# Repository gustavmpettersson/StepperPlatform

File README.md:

# StepperPlatform

This project considers a platform for moving microscopy samples. It is made as a Bachelor's thesis project at KTH. Usage instructions, drawings, and parts can be found in appendices.pdf

Contact me at gupet[a]kth.se or gustavpettersson[a]live.com

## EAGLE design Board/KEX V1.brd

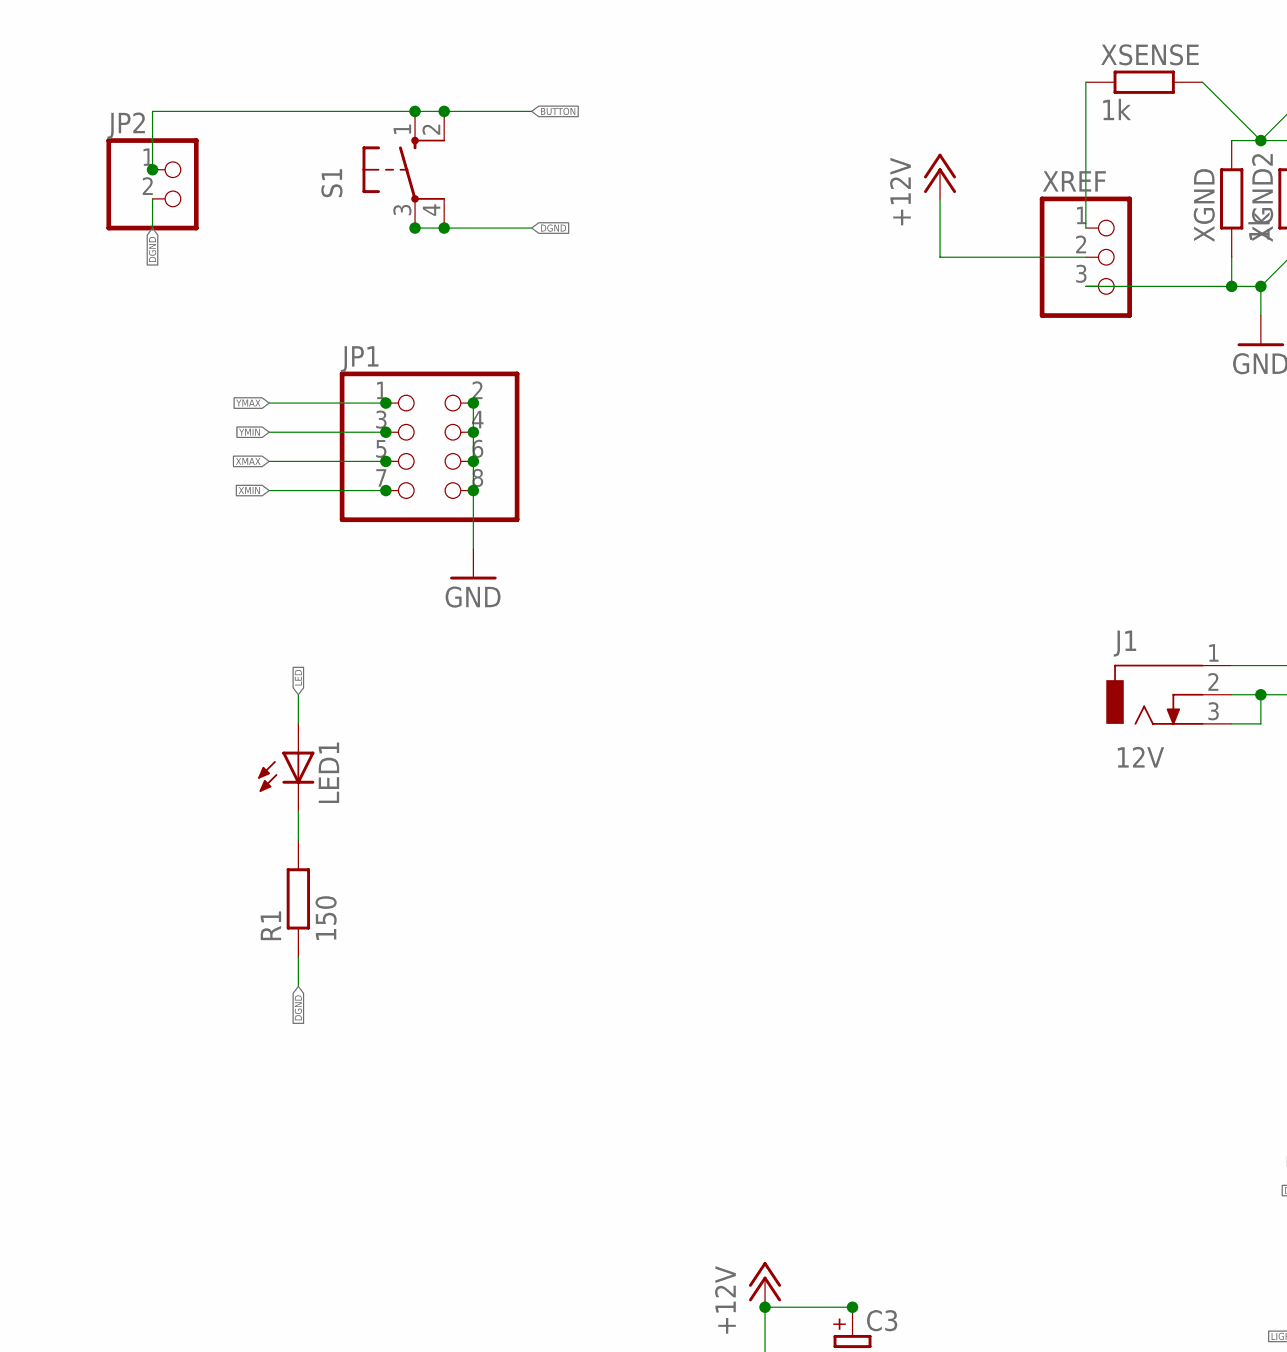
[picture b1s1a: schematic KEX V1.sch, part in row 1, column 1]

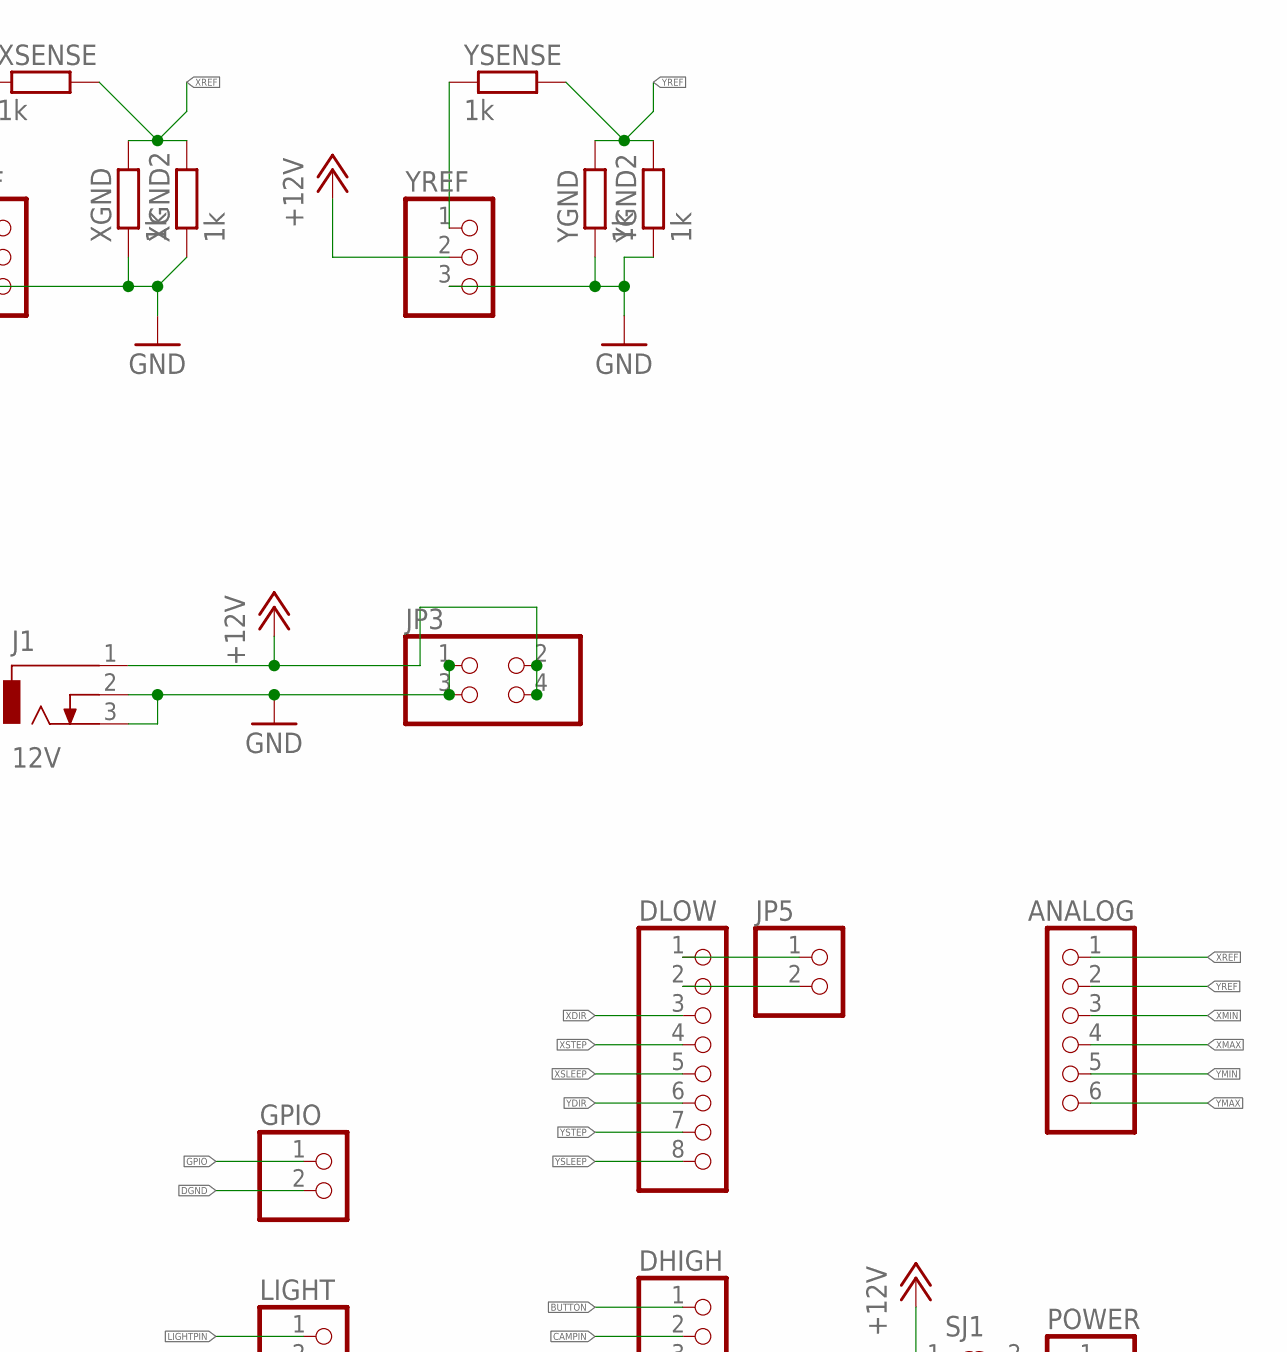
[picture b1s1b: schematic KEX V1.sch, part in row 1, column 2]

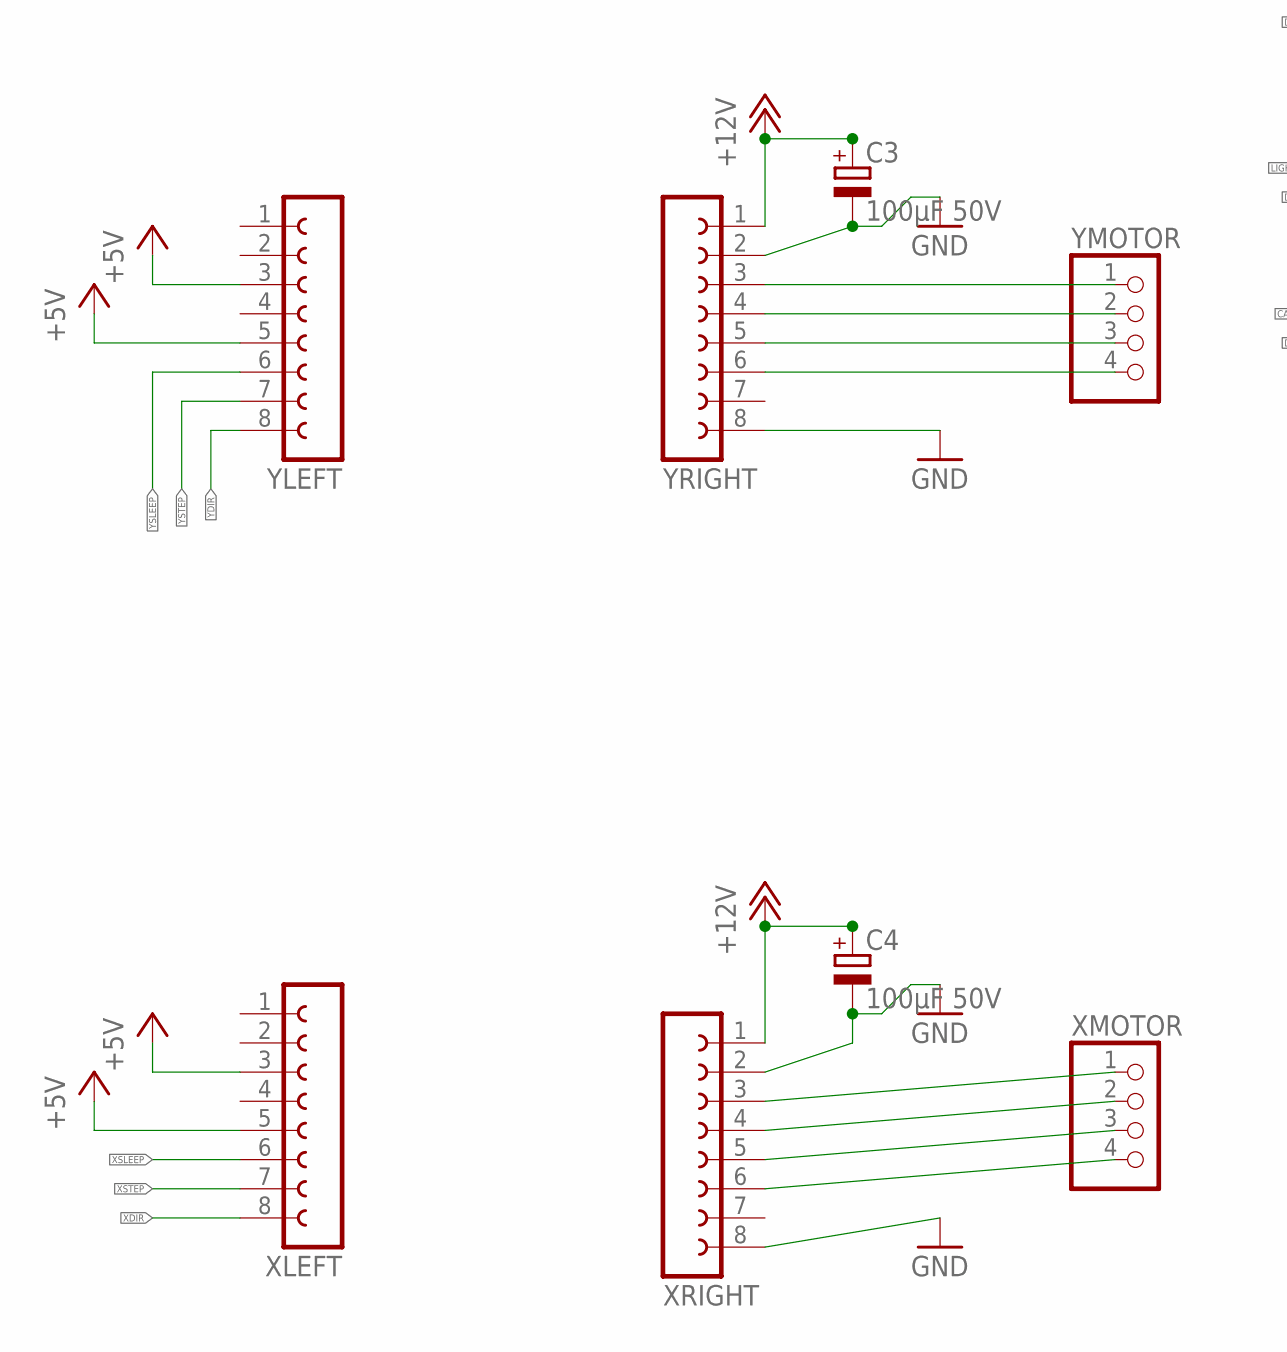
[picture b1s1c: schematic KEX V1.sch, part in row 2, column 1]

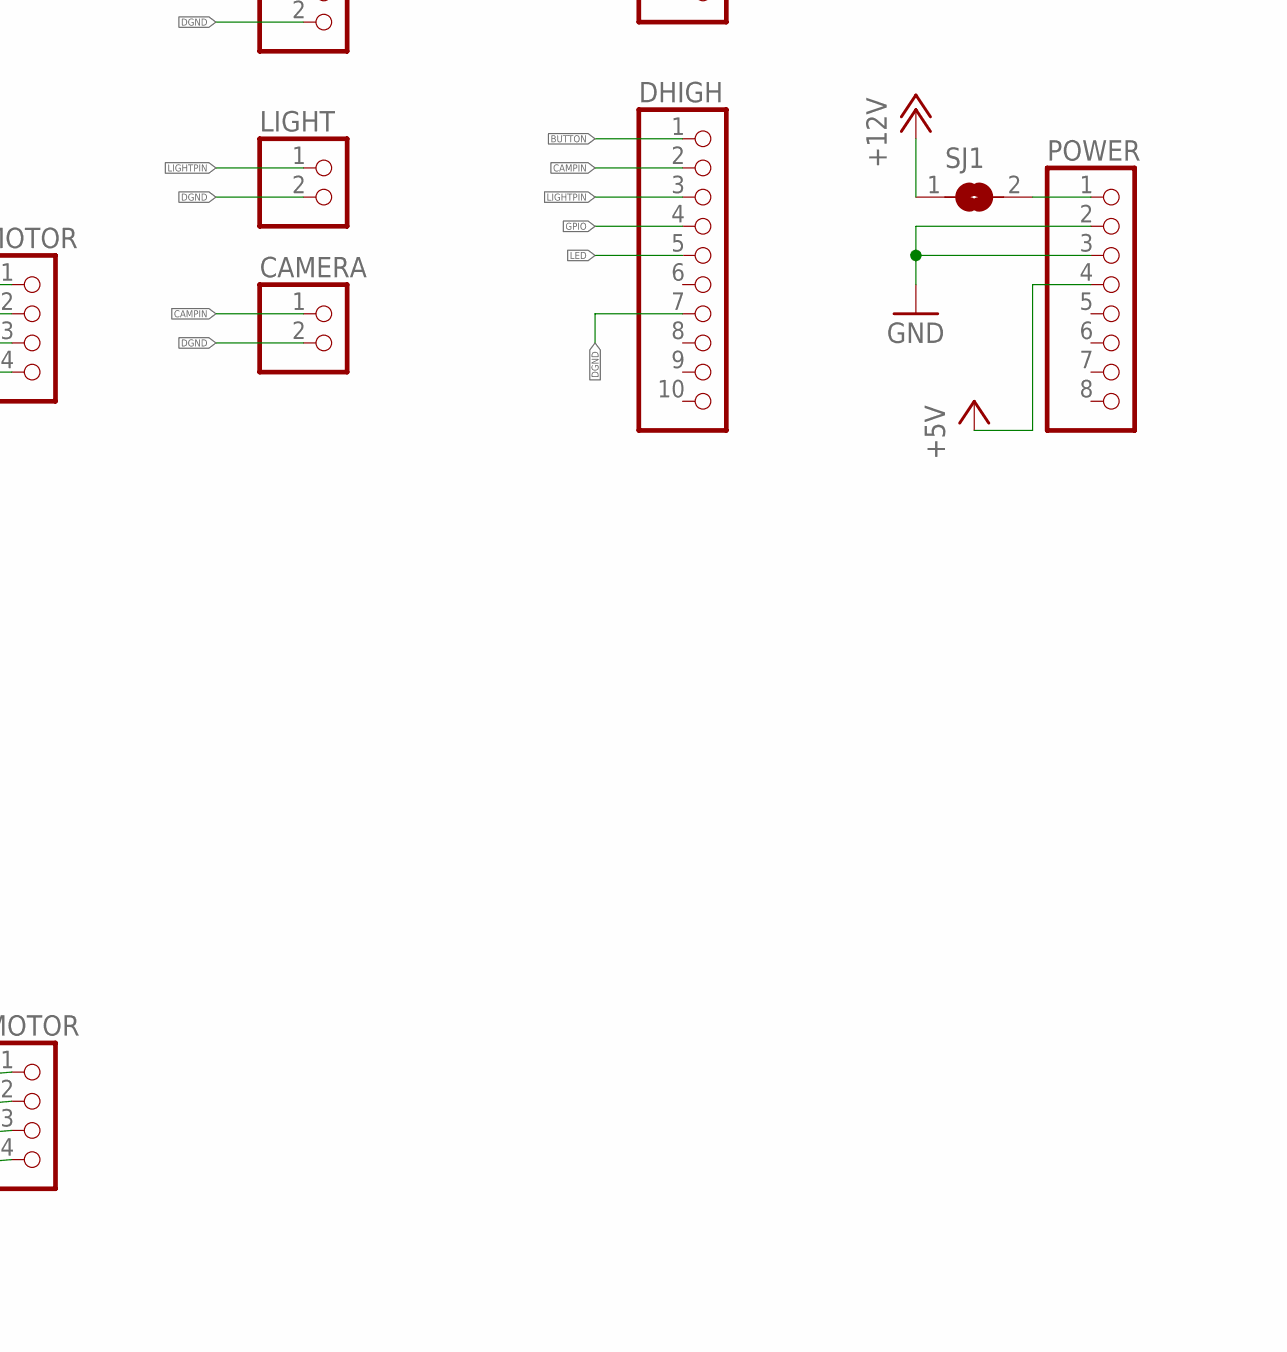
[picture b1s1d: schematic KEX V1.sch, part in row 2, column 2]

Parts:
ANALOG: PINHD-1X6; 1X06
C3, C4: 100µF 50V; E3,5-8
CAMERA: PINHD-1X2; 1X02
DHIGH: PINHD-1X10; 1X10
DLOW: PINHD-1X8; 1X08
GPIO: PINHD-1X2; 1X02
J1: 12V; DCJ0303
JP1: PINHD-2X4; 2X04
JP2, JP5: PINHD-1X2; 1X02
JP3: PINHD-2X2; 2X02
LED1: LED5MM
LIGHT: PINHD-1X2; 1X02
POWER: PINHD-1X8; 1X08
R1: 150; 0204/7
S1: 10-XX; B3F-10XX
SJ1: SJ
XGND, XGND2: 1k; 0204/7
XLEFT: FE08-1; FE08
XMOTOR: PINHD-1X4; 1X04
XREF: PINHD-1X3; 1X03
XRIGHT: FE08-1; FE08
XSENSE: 1k; 0204/7
YGND, YGND2: 1k; 0204/7
YLEFT: FE08-1; FE08
YMOTOR: PINHD-1X4; 1X04
YREF: PINHD-1X3; 1X03
YRIGHT: FE08-1; FE08
YSENSE: 1k; 0204/7

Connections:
+5V: POWER.4, XLEFT.3, XLEFT.5, YLEFT.3, YLEFT.5
+12V: C3.+, C4.+, J1.1, JP3.2, JP3.4, SJ1.1, XREF.2, XRIGHT.1, YREF.2, YRIGHT.1
BUTTON: DHIGH.1, JP2.1, S1.1 (S), S1.2 (S1)
CAMPIN: CAMERA.1, DHIGH.2
DGND: CAMERA.2, DHIGH.7, GPIO.2, JP2.2, LIGHT.2, R1.1, S1.3, S1.4 (P1)
GND: C3.-, C4.-, J1.2, J1.3, JP1.2, JP1.4, JP1.6, JP1.8, JP3.1, JP3.3, POWER.2, POWER.3, XGND.1, XGND2.1, XREF.3, XRIGHT.2, XRIGHT.8, YGND.1, YGND2.1, YREF.3, YRIGHT.2, YRIGHT.8
GPIO: DHIGH.4, GPIO.1
LED: DHIGH.5, LED1.A
LIGHTPIN: DHIGH.3, LIGHT.1
unnamed: XMOTOR.1, XRIGHT.3
unnamed: XMOTOR.2, XRIGHT.4
unnamed: XMOTOR.3, XRIGHT.5
unnamed: XMOTOR.4, XRIGHT.6
unnamed: DLOW.1, JP5.1
unnamed: DLOW.2, JP5.2
unnamed: YMOTOR.1, YRIGHT.3
unnamed: YMOTOR.2, YRIGHT.4
unnamed: YMOTOR.3, YRIGHT.5
unnamed: YMOTOR.4, YRIGHT.6
unnamed: LED1.K (C), R1.2
unnamed: POWER.1, SJ1.2
unnamed: XREF.1, XSENSE.1
unnamed: YREF.1, YSENSE.1
XDIR: DLOW.3, XLEFT.8
XMAX: ANALOG.4, JP1.5
XMIN: ANALOG.3, JP1.7
XREF: ANALOG.1, XGND.2, XGND2.2, XSENSE.2
XSLEEP: DLOW.5, XLEFT.6
XSTEP: DLOW.4, XLEFT.7
YDIR: DLOW.6, YLEFT.8
YMAX: ANALOG.6, JP1.1
YMIN: ANALOG.5, JP1.3
YREF: ANALOG.2, YGND.2, YGND2.2, YSENSE.2
YSLEEP: DLOW.8, YLEFT.6
YSTEP: DLOW.7, YLEFT.7

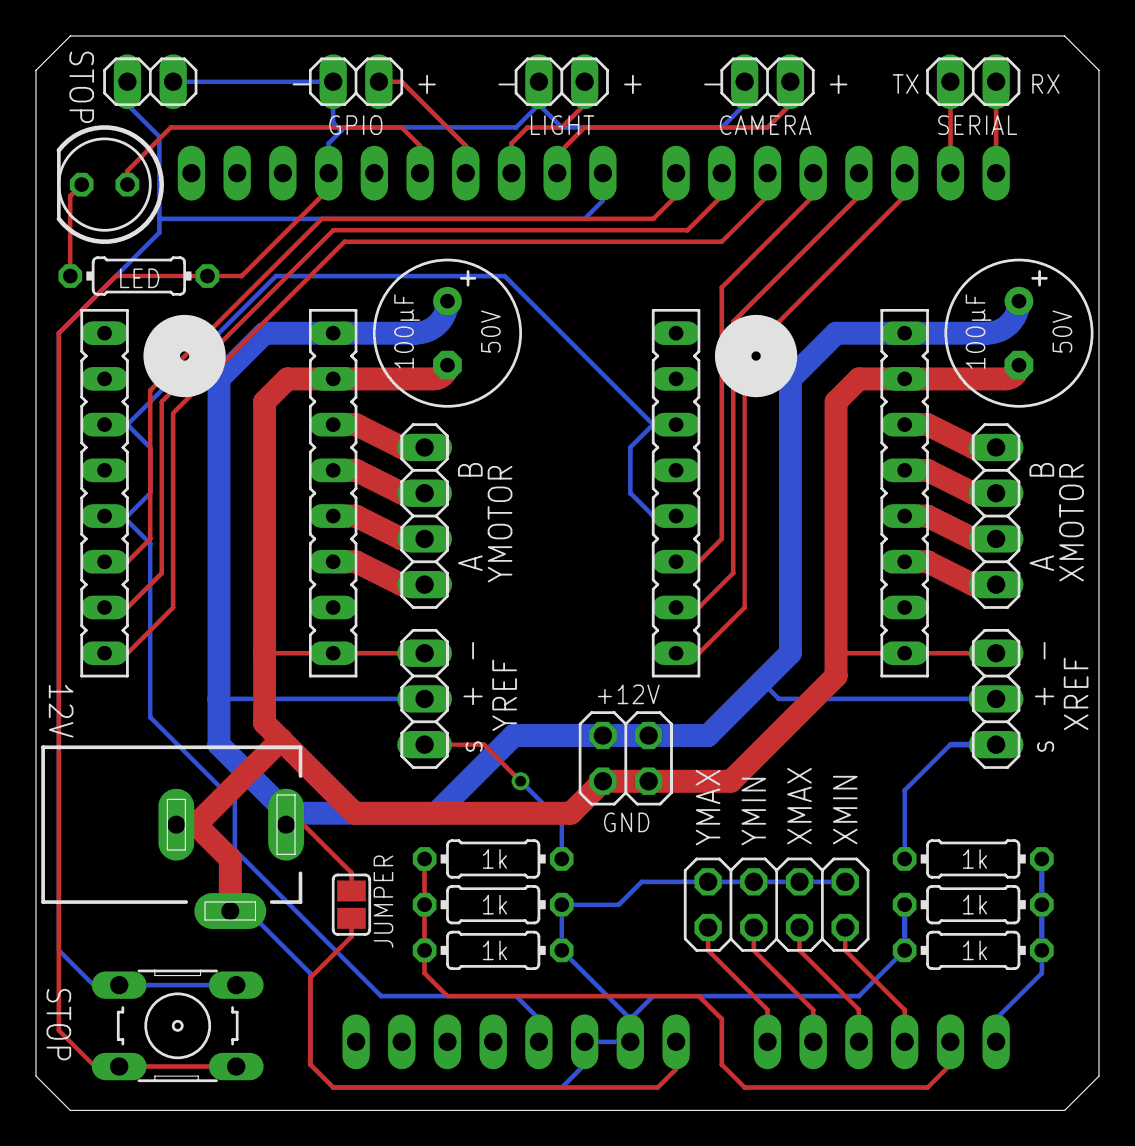
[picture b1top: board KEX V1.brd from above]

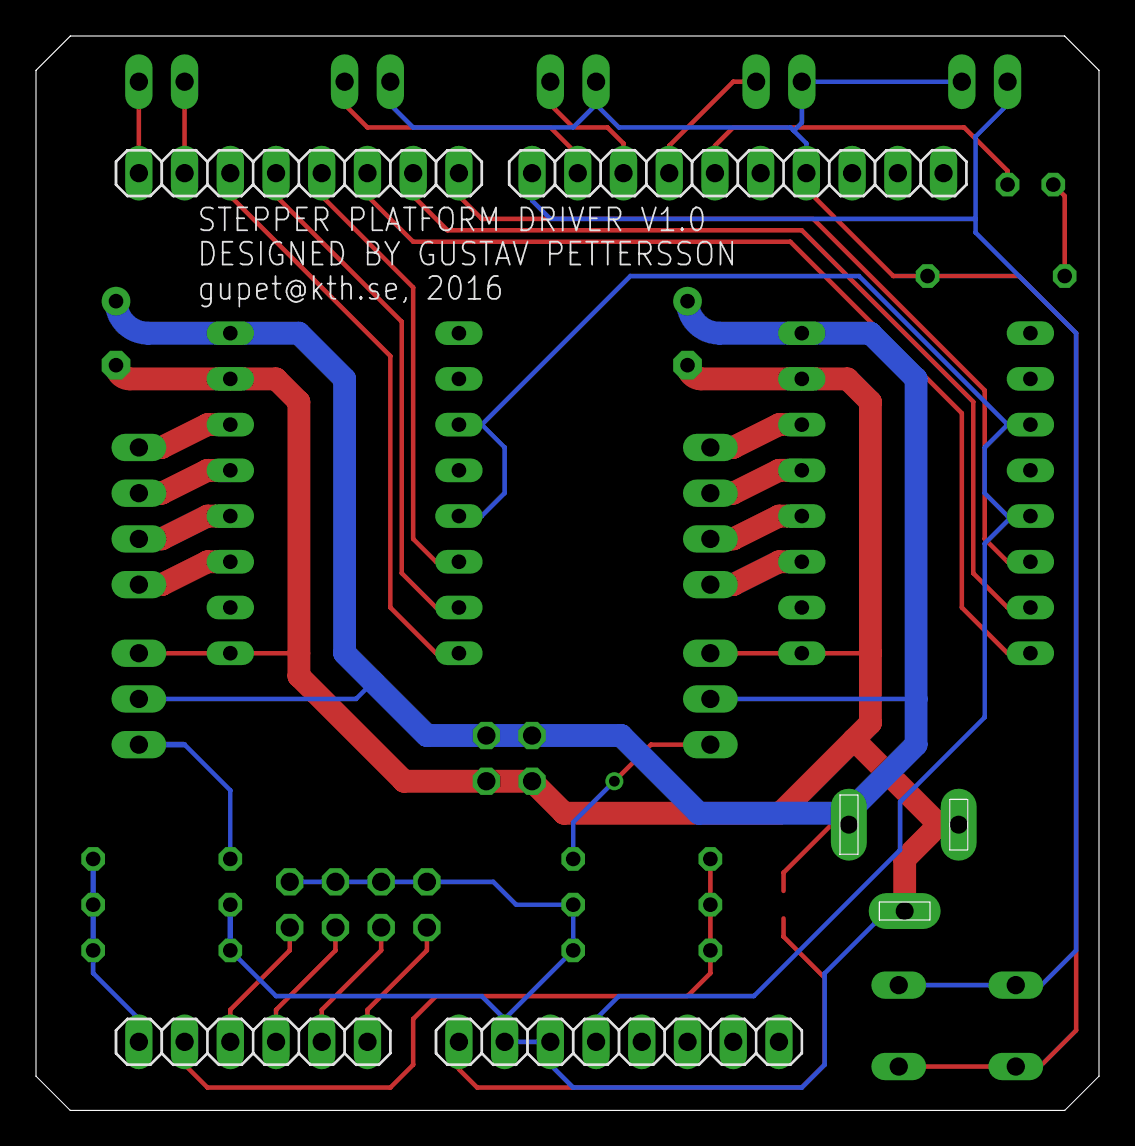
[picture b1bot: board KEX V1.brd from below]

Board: 2 copper layers, 59.1 x 59.7 mm, 32 parts (4 on the bottom side), 35 nets.

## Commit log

2016-04-30 Added files via upload
2016-04-30 Rename KEX V1.sch to Board/KEX V1.sch
2016-04-30 Rename KEX V1.brd to Board/KEX V1.brd
2016-05-02 Create placeholder
